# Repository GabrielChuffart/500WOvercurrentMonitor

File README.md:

**500 W overcurrent monitor**
E-Agle TRT recruitment - Gabriel Chuffart - KiCad 10

**Overview**
A hardware-only monitor (no programmable logic) that opens a relay in series with the load
as soon as the load could exceed 500 W, and keeps it open until the monitor is power-cycled.
The load current is measured by an Allegro ACS781 Hall-effect sensor and compared with two
thresholds, a NAND-gate latch then drives the relay.

**Principle**
ACS781 Hall sensor (U401) -> RC filter -> two comparators (U501) -> NAND latch (U503) -> coil driver (Q301, Q302) → relay K301.

**Circuit characteristics:**
- Trip at 8.7A : 500W / 48V = 10.42A, minus the ±1.59A worst-case error -> It trips between 7.1 and 10.3A, so never above 500W from 24 to 48V.
- latch cleared only at power-up, by MAX809S supervisor (U502).
- Fail-safe: a dead or disconnected sensor (V_SENSE < 0.84V) also trips.
- Coil driven at a constant ~78mA from 9 to 17V
- Input: resettable fuse, TVS, P-MOSFET reverse-polarity protection, 3.3V LDO.

# Recruitment for E-Agle TRT | Electronics division

Welcome to the recruitment _test_ for the electronics team of E-Agle Trento Racing Team.

This _test_ is meant to give us the possibility to have a first understanding of the capabilities of our applicants without them having the pressure of seeing it as an exam.

Moreover it's studied so that the applicants get a first taste of the tools used, so that once in the team, they can get up and running quickly into the team's workflow without having to learn stuff under pressure when it's needed.

## What we'll look into

 - Understanding of basic electronics
 - Components choice and their suitability
 - KiCad
   - Schematic choices, tidyness and good practices
   - Board layout understanding and, again, good practices
 - `git` usage: fork, branch, clone, commit, push, pull
 - Not only _tecnical correctness_ but also actual usability.

## Assignment

Develop an overcurrent monitoring system (**monitor**) to perform plauysibility checks of a secondary system (**load**).

### Overview
The **monitor** has the following specs:
- It is supplied by an unstable DC voltage line, ranging from 9V to 17V
- Has a normally open relay connected in series with the load
- Has a hall effect sensor that measures the current through the load

The **load** has the following specs:
- Voltage range: $24[V] \div 48[V]$
- Current range: $-3[A] \div 25[A]$

### Specs
The **monitor** must ensure that the relay is open if the power obsorbed by the **load** is above $500[W]$.
Once open, it must not be possible to close the relay unless the **monitor** is power cycled.

No programmable logic is allowed.

The Hall effect based sensor can be chosen from the _Allegro ACS781xLR_ family of devices. Other sensors may be used as long as the specs are met and equivalency is proven.

Below you can find a general diagram of the system

## KiCad instructions
- In the schematic use also a hierarchical sheet
  - _It's not a good practice for such a small project, but it's for letting you learn about hierarchy without the hassle of a more complex assignment_

- Add comments for the necessary calculations of values

- Consider JLC PCB as the board manufacturer

## General instructions

 - Create a repository on your GitHub account (if you don't have it, create one) and copy this project in it. **Do not clone this repository!**
 - Branch the master into one called `name_surname` and commit your progress in this branch
 - Commit your progress along the way. **Do not commit just the finished project**, use Git for what it's made for!
 - When you are done, generate the schematic output inside `docs/` and the production (gerber) files in `output/`
 - If you haven't already, submit your application form [here](https://eagletrt.it/apply)
 - If you have any questions feel free to contact us at [electronics@eagletrt.it](mailto:electronics@eagletrt.it)
 - Feel free to also come to our lab (Povo 2 floor -2) if we are slow at replying
 - You have **2 weeks** (14 days) to work on this project (**This is a hard deadline and we evaluate if you meet deadlines**)

## Links
:globe_with_meridians: [Website](https://www.eagletrt.it)

:iphone: [Instagram](https://www.instagram.com/eagletrt)

:computer: [LinkedIn](https://www.linkedin.com/company/eagletrentoracingteam)

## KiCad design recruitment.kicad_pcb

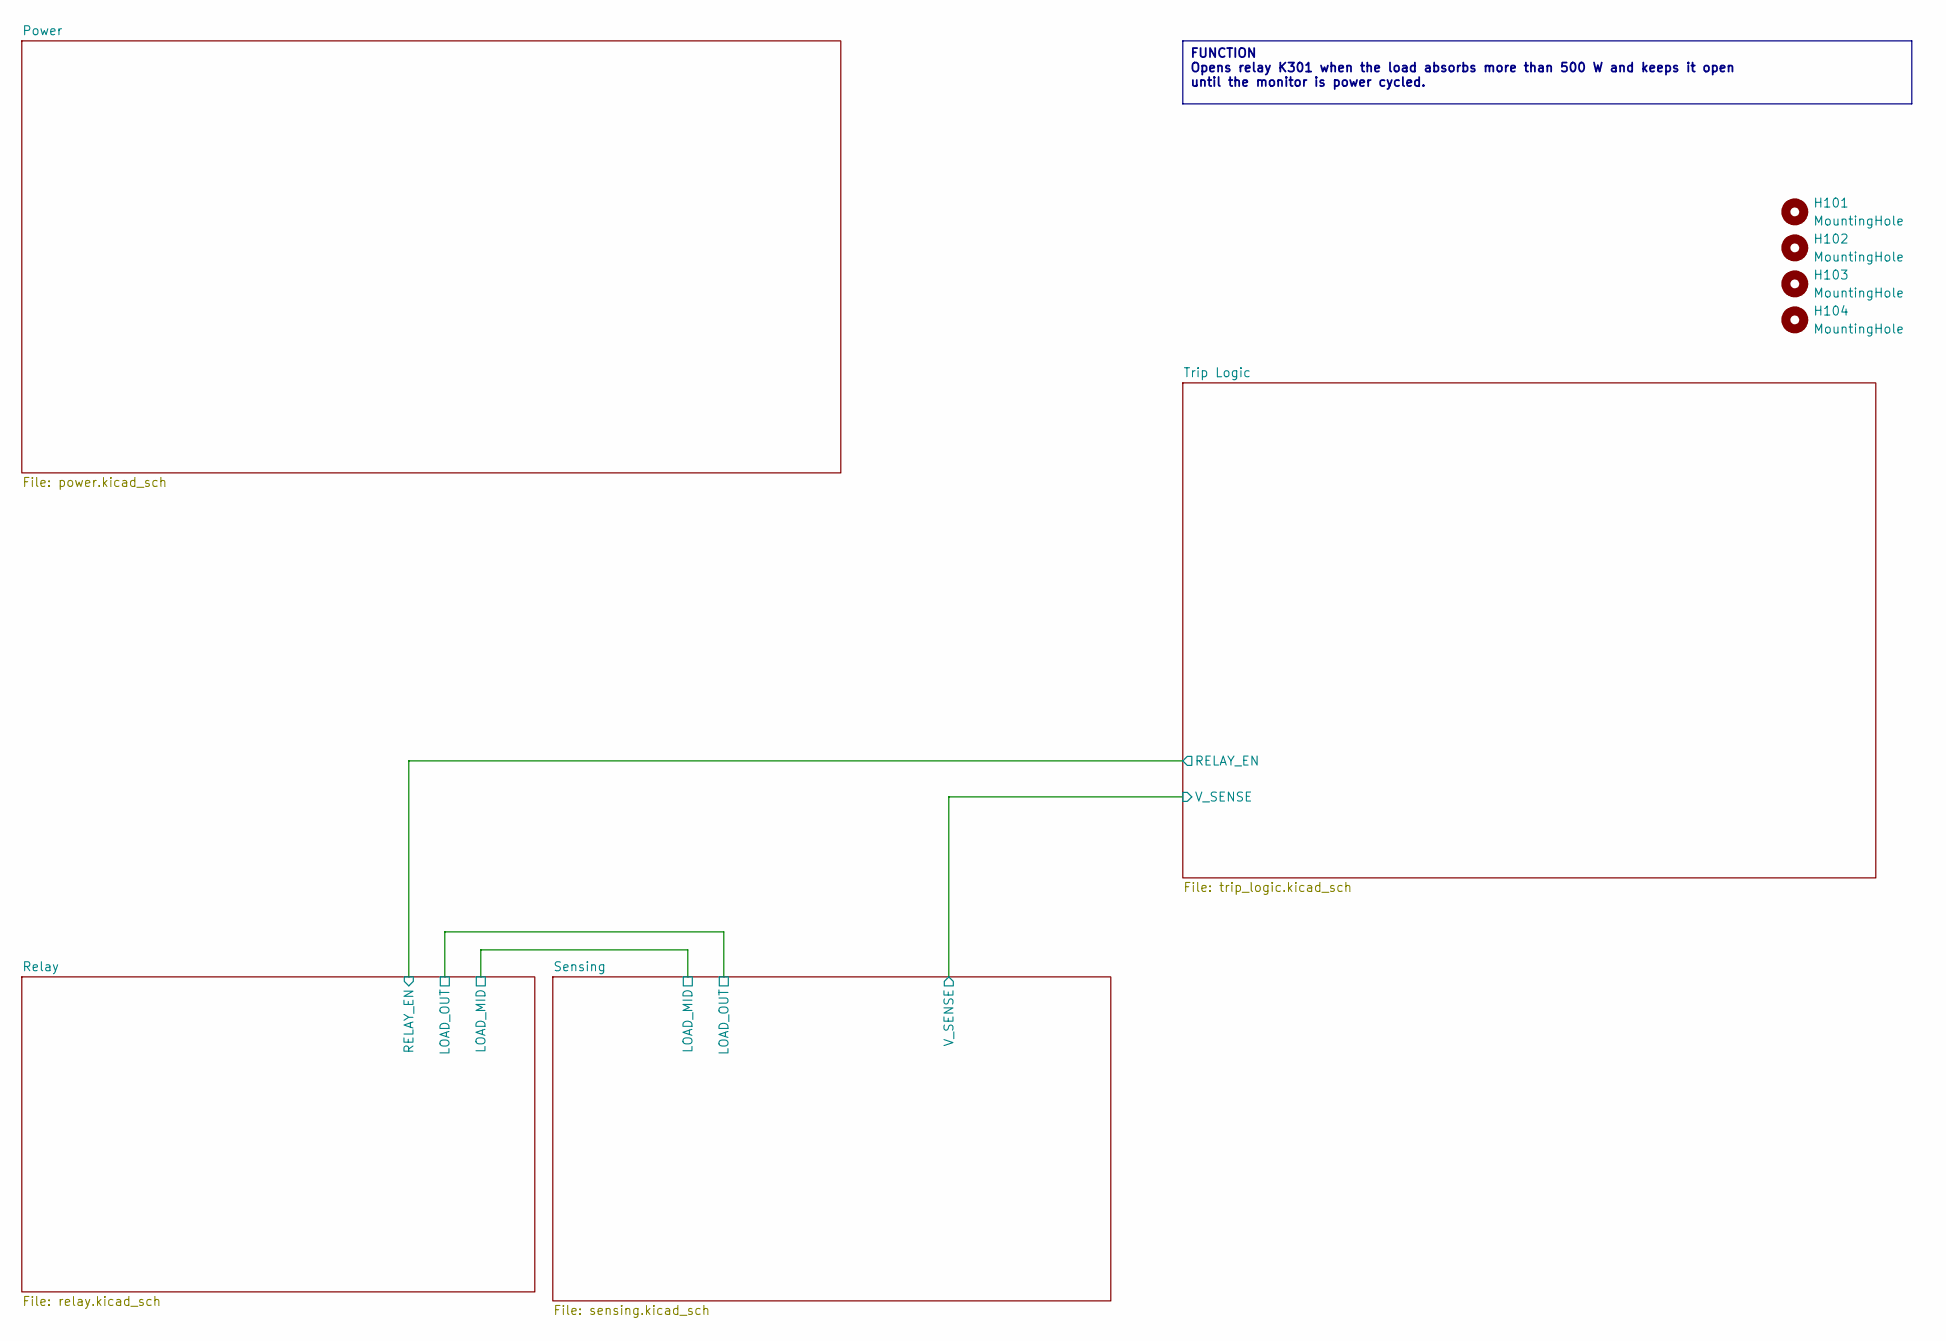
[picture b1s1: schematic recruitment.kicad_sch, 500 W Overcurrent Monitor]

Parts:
H101, H102, H103, H104: MountingHole; MountingHole_3.2mm_M3

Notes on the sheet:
FUNCTION Opens relay K301 when the load absorbs more than 500 W and keeps it open until the monitor is power cycled.

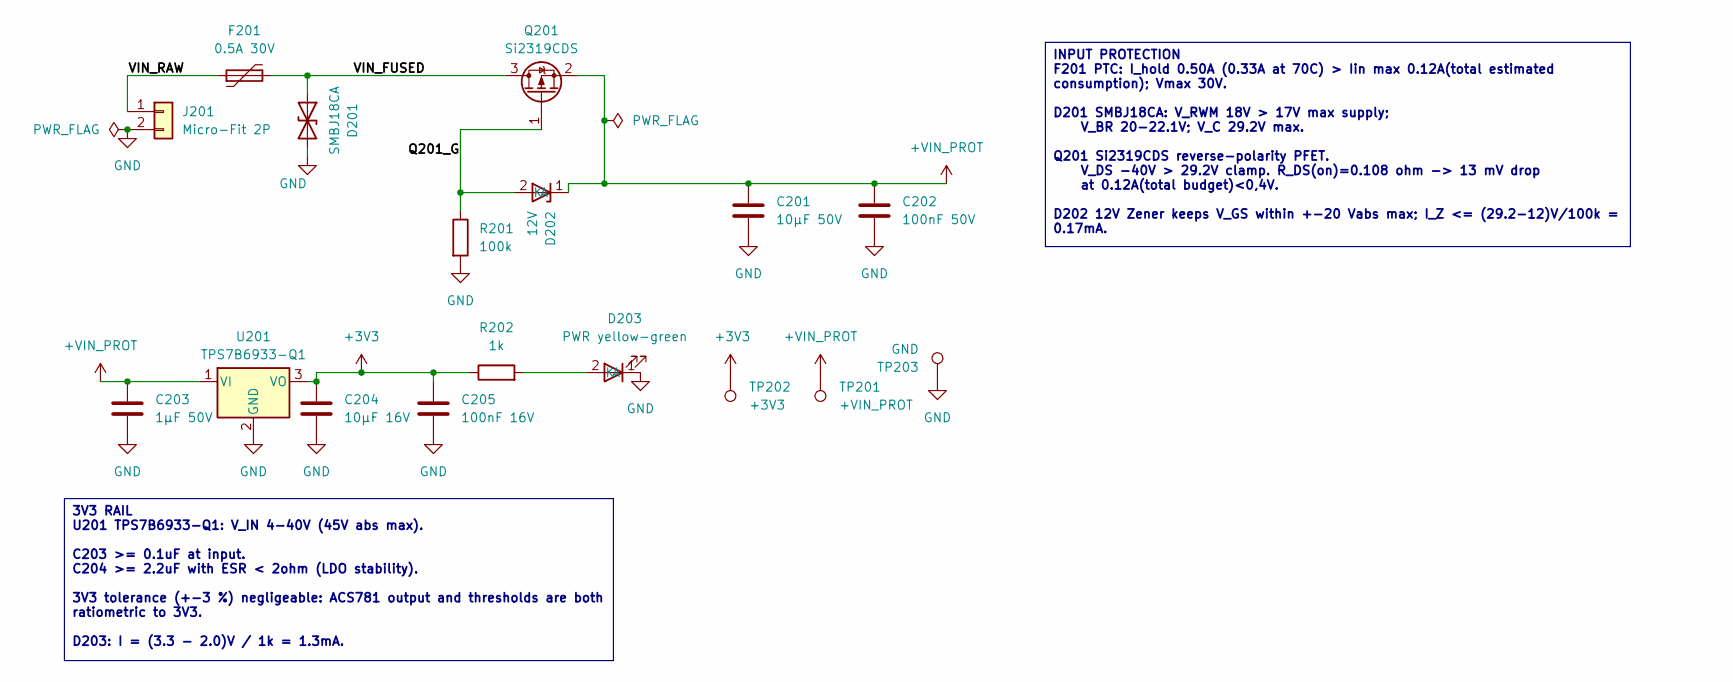
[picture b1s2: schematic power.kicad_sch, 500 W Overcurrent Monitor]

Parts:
C201: 10µF 50V; C_1210_3225Metric
C202: 100nF 50V; C_0603_1608Metric
C203: 1µF 50V; C_0805_2012Metric
C204: 10µF 16V; C_0805_2012Metric
C205: 100nF 16V; C_0603_1608Metric
D201: SMBJ18CA; D_SMB
D202: 12V; D_SOD-123
D203: PWR yellow-green; LED_0603_1608Metric
F201: 0.5A 30V; Fuse_1812_4532Metric
J201: Micro-Fit 2P; Molex_Micro-Fit_3.0_43650-0215_1x02_P3.00mm_Vertical
Q201: Si2319CDS; SOT-23
R201: 100k; R_0603_1608Metric
R202: 1k; R_0603_1608Metric
TP201: +VIN_PROT; TestPoint_Pad_D1.5mm
TP202: +3V3; TestPoint_Pad_D1.5mm
TP203: GND; TestPoint_Keystone_5000-5004_Miniature
U201: TPS7B6933-Q1; SOT-223-3_TabPin2; MPN TPS7B6933QDCYRQ1

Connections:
+3V3: C204.1, C205.1, R202.1, TP202.1 (1_1), U201.3 (VO); also elsewhere on the board
+VIN_PROT: C201.1, C202.1, C203.1, D202.1 (K), Q201.2 (S), TP201.1 (1_1), U201.1 (VI); also elsewhere on the board
/Power/Q201_G: D202.2 (A), Q201.1 (G), R201.1
/Power/VIN_FUSED: D201.1 (A1), F201.2, Q201.3 (D)
/Power/VIN_RAW: F201.1, J201.1
GND: C201.2, C202.2, C203.2, C204.2, C205.2, D201.2 (A2), D203.1 (K), J201.2, R201.2, TP203.1 (1_1), U201.2 (GND); also elsewhere on the board
unnamed: D203.2 (A), R202.2

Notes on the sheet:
INPUT PROTECTION F201 PTC: I_hold 0.50A (0.33A at 70C) > Iin max 0.12A(total estimated consumption); Vmax 30V. D201 SMBJ18CA: V_RWM 18V > 17V max supply; V_BR 20-22.1V; V_C 29.2V max. Q201 Si2319CDS reverse-polarity PFET. V_DS -40V > 29.2V clamp. R_DS(on)=0.108 ohm -> 13 mV drop at 0.12A(total budg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
3V3 RAIL U201 TPS7B6933-Q1: V_IN 4-40V (45V abs max). C203 >= 0.1uF at input. C204 >= 2.2uF with ESR < 2ohm (LDO stability). 3V3 tolerance (+-3 %) negligeable: ACS781 output and thresholds are both ratiometric to 3V3. D203: I = (3.3 - 2.0)V / 1k = 1.3mA.

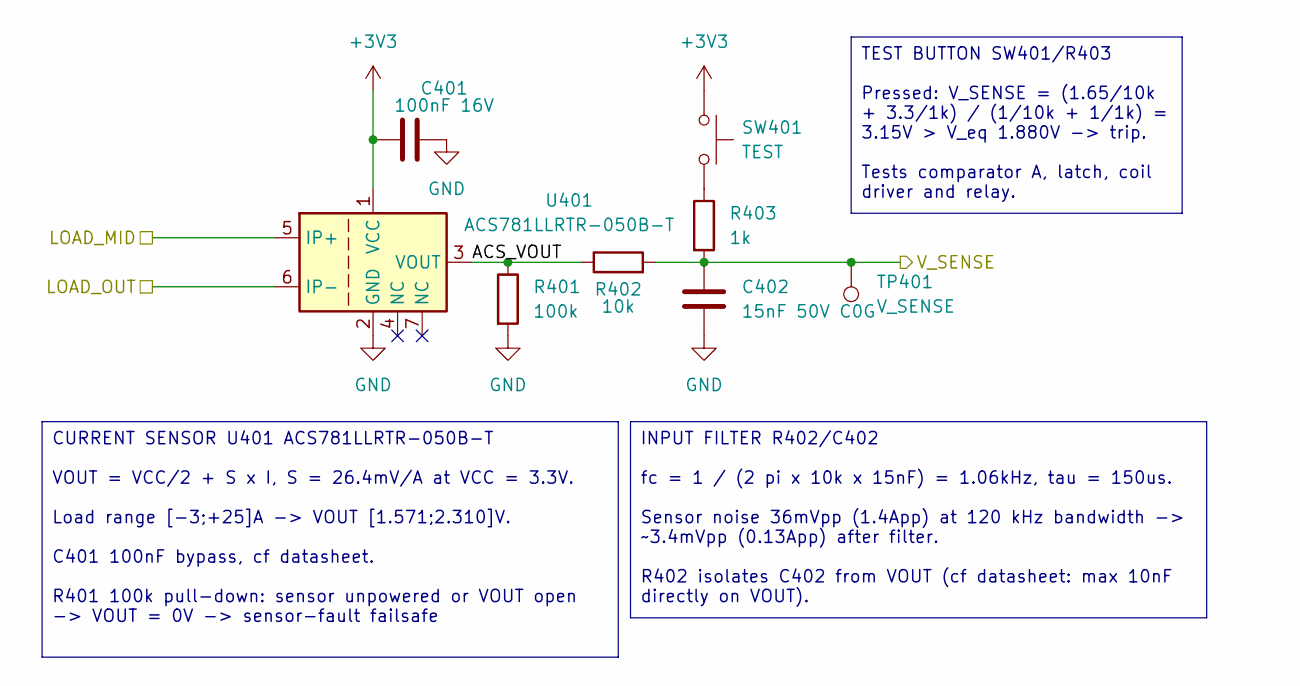
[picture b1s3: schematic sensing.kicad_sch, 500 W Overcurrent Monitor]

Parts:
C401: 100nF 16V; C_0603_1608Metric
C402: 15nF 50V C0G; C_0603_1608Metric
R401: 100k; R_0603_1608Metric
R402: 10k; R_0603_1608Metric
R403: 1k; R_0603_1608Metric
SW401: TEST; SW_SPST_PTS645Sx43SMTR92
TP401: V_SENSE; TestPoint_Pad_D1.5mm
U401: ACS781LLRTR-050B-T; Allegro_PSOF-7_4.8x6.4mm_P1.60mm; MPN ACS781LLRTR-050B-T

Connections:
+3V3: C401.1, SW401.1, U401.1 (VCC); also elsewhere on the board
/Relay/LOAD_MID: U401.5 (IP+); also elsewhere on the board
/Relay/LOAD_OUT: U401.6 (IP-); also elsewhere on the board
/Sensing/ACS_VOUT: R401.1, R402.1, U401.3 (VOUT)
/Sensing/V_SENSE: C402.1, R402.2, R403.2, TP401.1 (1_1); also elsewhere on the board
GND: C401.2, C402.2, R401.2, U401.2 (GND); also elsewhere on the board
unnamed: R403.1, SW401.2

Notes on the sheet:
CURRENT SENSOR U401 ACS781LLRTR-050B-T VOUT = VCC/2 + S x I, S = 26.4mV/A at VCC = 3.3V. Load range [-3;+25]A -> VOUT [1.571;2.310]V. C401 100nF bypass, cf datasheet. R401 100k pull-down: sensor unpowered or VOUT open -> VOUT = 0V -> sensor-fault failsafe
TEST BUTTON SW401/R403 Pressed: V_SENSE = (1.65/10k + 3.3/1k) / (1/10k + 1/1k) = 3.15V > V_eq 1.880V -> trip. Tests comparator A, latch, coil driver and relay.
INPUT FILTER R402/C402 fc = 1 / (2 pi x 10k x 15nF) = 1.06kHz, tau = 150us. Sensor noise 36mVpp (1.4App) at 120 kHz bandwidth -> ~3.4mVpp (0.13App) after filter. R402 isolates C402 from VOUT (cf datasheet: max 10nF directly on VOUT).

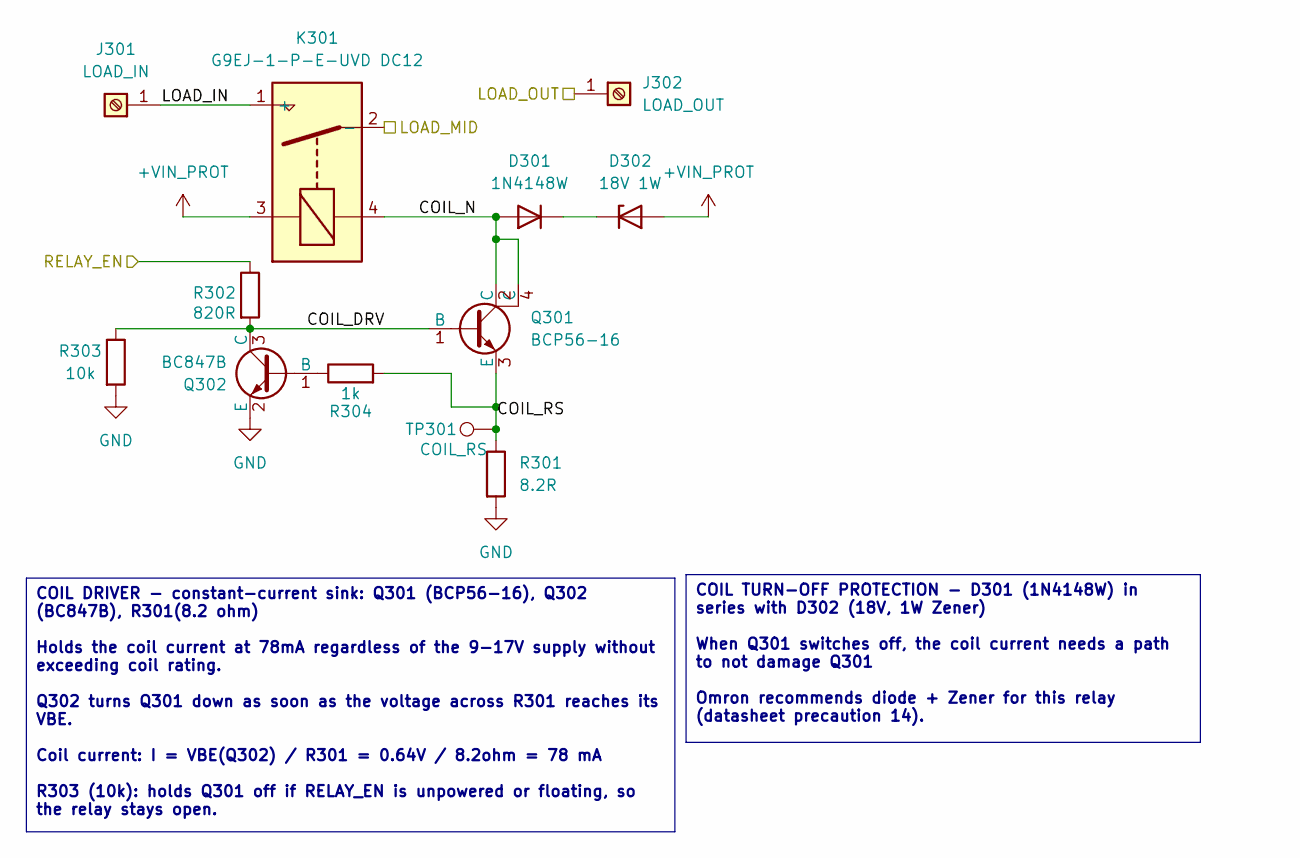
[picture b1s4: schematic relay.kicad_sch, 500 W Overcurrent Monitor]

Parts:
D301: 1N4148W; D_SOD-123
D302: 18V 1W; D_SMA
J301: LOAD_IN; MountingHole_4.3mm_M4_Pad
J302: LOAD_OUT; MountingHole_4.3mm_M4_Pad
K301: G9EJ-1-P-E-UVD DC12; Relay_Omron_G9EJ-1-P-E; MPN G9EJ-1-P-E-UVD DC12
Q301: BCP56-16; SOT-223
Q302: BC847B; SOT-23
R301: 8.2R; R_0805_2012Metric
R302: 820R; R_0603_1608Metric
R303: 10k; R_0603_1608Metric
R304: 1k; R_0603_1608Metric
TP301: COIL_RS; TestPoint_Pad_D1.5mm

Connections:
+VIN_PROT: D302.2 (A), K301.3; also elsewhere on the board
/Relay/COIL_DRV: Q301.1 (B), Q302.3 (C), R302.2, R303.1
/Relay/COIL_N: D301.2 (A), K301.4, Q301.2 (C), Q301.4 (C)
/Relay/COIL_RS: Q301.3 (E), R301.1, R304.2, TP301.1 (1_1)
/Relay/LOAD_IN: J301.1 (Pin_1_1), K301.1 (+)
/Relay/LOAD_MID: K301.2 (-); also elsewhere on the board
/Relay/LOAD_OUT: J302.1 (Pin_1_1); also elsewhere on the board
/Relay/RELAY_EN: R302.1; also elsewhere on the board
GND: Q302.2 (E), R301.2, R303.2; also elsewhere on the board
unnamed: D301.1 (K), D302.1 (K)
unnamed: Q302.1 (B), R304.1

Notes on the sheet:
COIL TURN-OFF PROTECTION - D301 (1N4148W) in series with D302 (18V, 1W Zener) When Q301 switches off, the coil current needs a path to not damage Q301 Omron recommends diode + Zener for this relay (datasheet precaution 14).
COIL DRIVER - constant-current sink: Q301 (BCP56-16), Q302 (BC847B), R301(8.2 ohm) Holds the coil current at 78mA regardless of the 9-17V supply without exceeding coil rating. Q302 turns Q301 down as soon as the voltage across R301 reaches its VBE. Coil current: I = VBE(Q302) / R301 = 0.64V / 8.2oh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

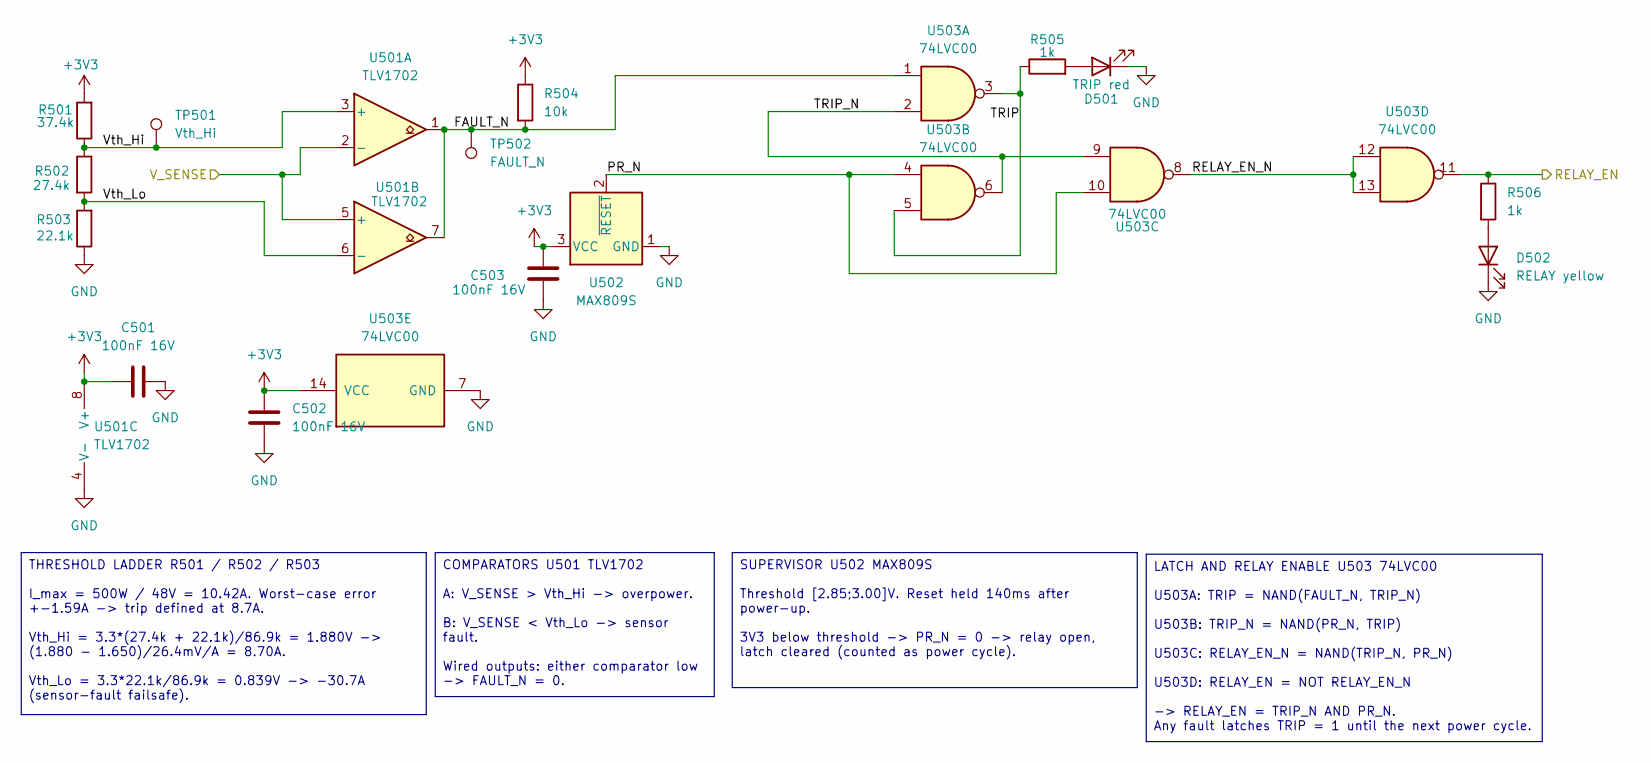
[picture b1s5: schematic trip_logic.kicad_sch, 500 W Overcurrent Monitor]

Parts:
C501, C502, C503: 100nF 16V; C_0603_1608Metric
D501: TRIP red; LED_0603_1608Metric
D502: RELAY yellow; LED_0603_1608Metric
R501: 37.4k; R_0603_1608Metric
R502: 27.4k; R_0603_1608Metric
R503: 22.1k; R_0603_1608Metric
R504: 10k; R_0603_1608Metric
R505, R506: 1k; R_0603_1608Metric
TP501: Vth_Hi; TestPoint_Pad_D1.5mm
TP502: FAULT_N; TestPoint_Pad_D1.5mm
U501: TLV1702; VSSOP-8_3x3mm_P0.65mm; MPN TLV1702AIDGKR
U502: MAX809S; SOT-23; MPN MAX809STRG
U503: 74LVC00; SOIC-14_3.9x8.7mm_P1.27mm; MPN SN74LVC00ADR

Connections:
+3V3: C501.1, C502.1, C503.2, R501.2, R504.1, U501.8 (V+), U502.3 (VCC), U503.14 (VCC); also elsewhere on the board
/Relay/RELAY_EN: R506.1, U503.11; also elsewhere on the board
/Sensing/V_SENSE: U501.2 (-), U501.5 (+); also elsewhere on the board
/Trip Logic/FAULT_N: R504.2, TP502.1 (1_1), U501.1, U501.7, U503.1
/Trip Logic/PR_N: U502.2 (~RESET), U503.4, U503.10
/Trip Logic/RELAY_EN_N: U503.8, U503.12, U503.13
/Trip Logic/TRIP: R505.1, U503.3, U503.5
/Trip Logic/TRIP_N: U503.2, U503.6, U503.9
/Trip Logic/Vth_Hi: R501.1, R502.1, TP501.1 (1_1), U501.3 (+)
/Trip Logic/Vth_Lo: R502.2, R503.2, U501.6 (-)
GND: C501.2, C502.2, C503.1, D501.1 (K), D502.1 (K), R503.1, U501.4 (V-), U502.1 (GND), U503.7 (GND); also elsewhere on the board
unnamed: D501.2 (A), R505.2
unnamed: D502.2 (A), R506.2

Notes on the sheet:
SUPERVISOR U502 MAX809S Threshold [2.85;3.00]V. Reset held 140ms after power-up. 3V3 below threshold -> PR_N = 0 -> relay open, latch cleared (counted as power cycle).
THRESHOLD LADDER R501 / R502 / R503 I_max = 500W / 48V = 10.42A. Worst-case error +-1.59A -> trip defined at 8.7A. Vth_Hi = 3.3*(27.4k + 22.1k)/86.9k = 1.880V -> (1.880 - 1.650)/26.4mV/A = 8.70A. Vth_Lo = 3.3*22.1k/86.9k = 0.839V -> -30.7A (sensor-fault failsafe).
COMPARATORS U501 TLV1702 A: V_SENSE > Vth_Hi -> overpower. B: V_SENSE < Vth_Lo -> sensor fault. Wired outputs: either comparator low -> FAULT_N = 0.
LATCH AND RELAY ENABLE U503 74LVC00 U503A: TRIP = NAND(FAULT_N, TRIP_N) U503B: TRIP_N = NAND(PR_N, TRIP) U503C: RELAY_EN_N = NAND(TRIP_N, PR_N) U503D: RELAY_EN = NOT RELAY_EN_N -> RELAY_EN = TRIP_N AND PR_N. Any fault latches TRIP = 1 until the next power cycle.

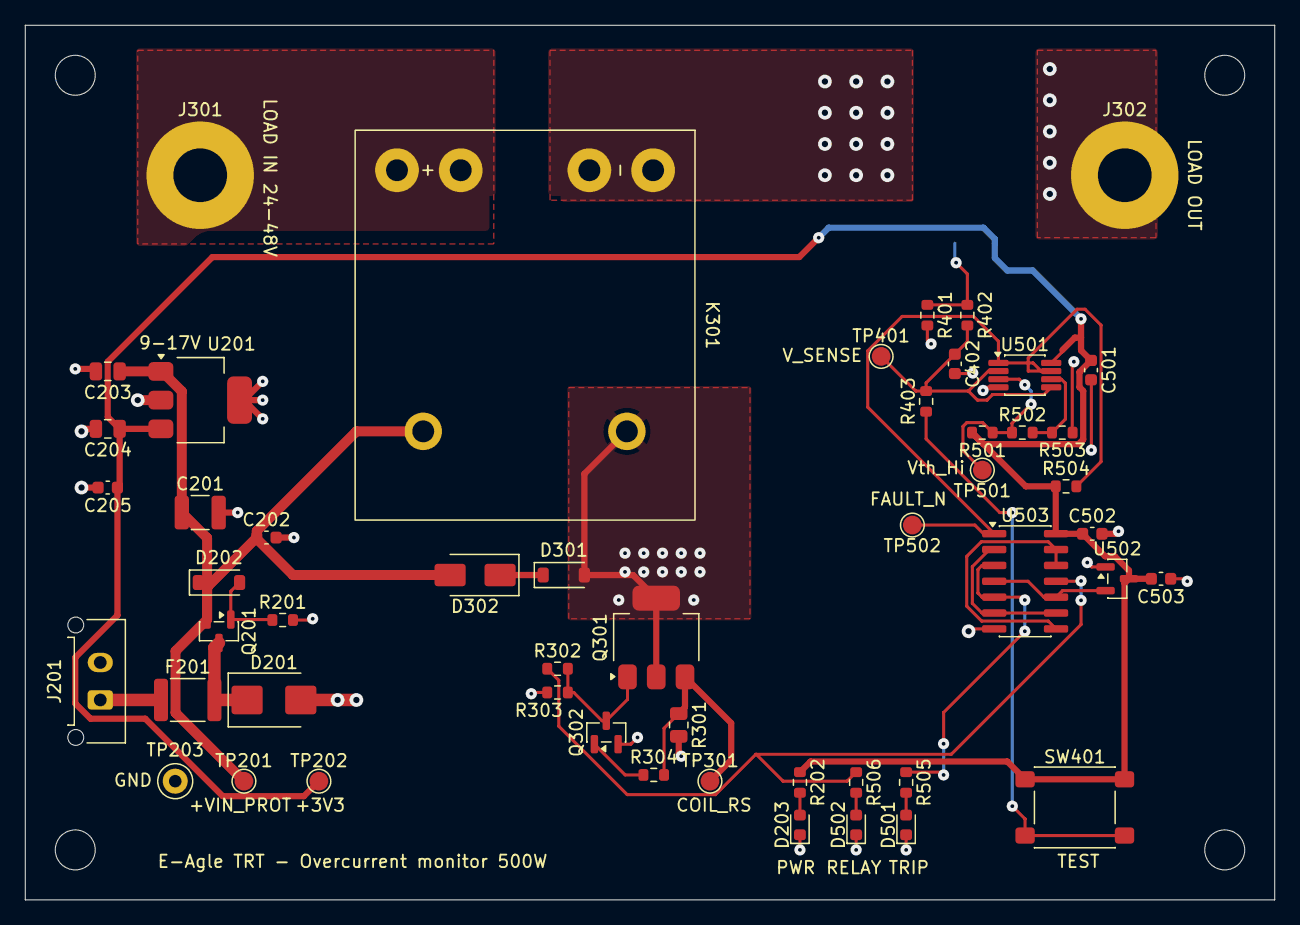
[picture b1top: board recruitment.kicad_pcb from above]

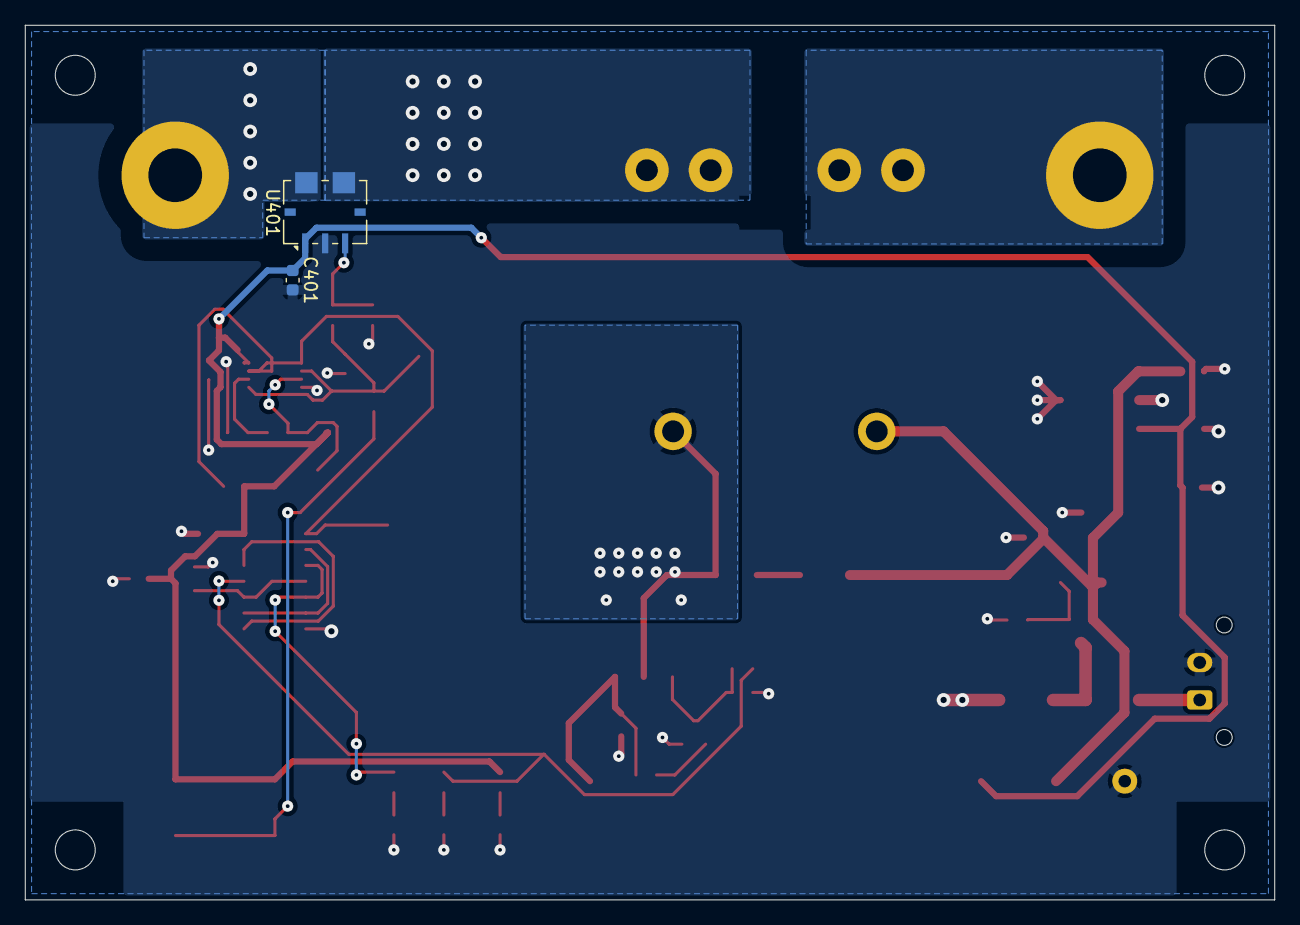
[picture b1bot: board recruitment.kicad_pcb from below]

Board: 2 copper layers, 100.0 x 70.0 mm, 57 parts (2 on the bottom side), 28 nets.
